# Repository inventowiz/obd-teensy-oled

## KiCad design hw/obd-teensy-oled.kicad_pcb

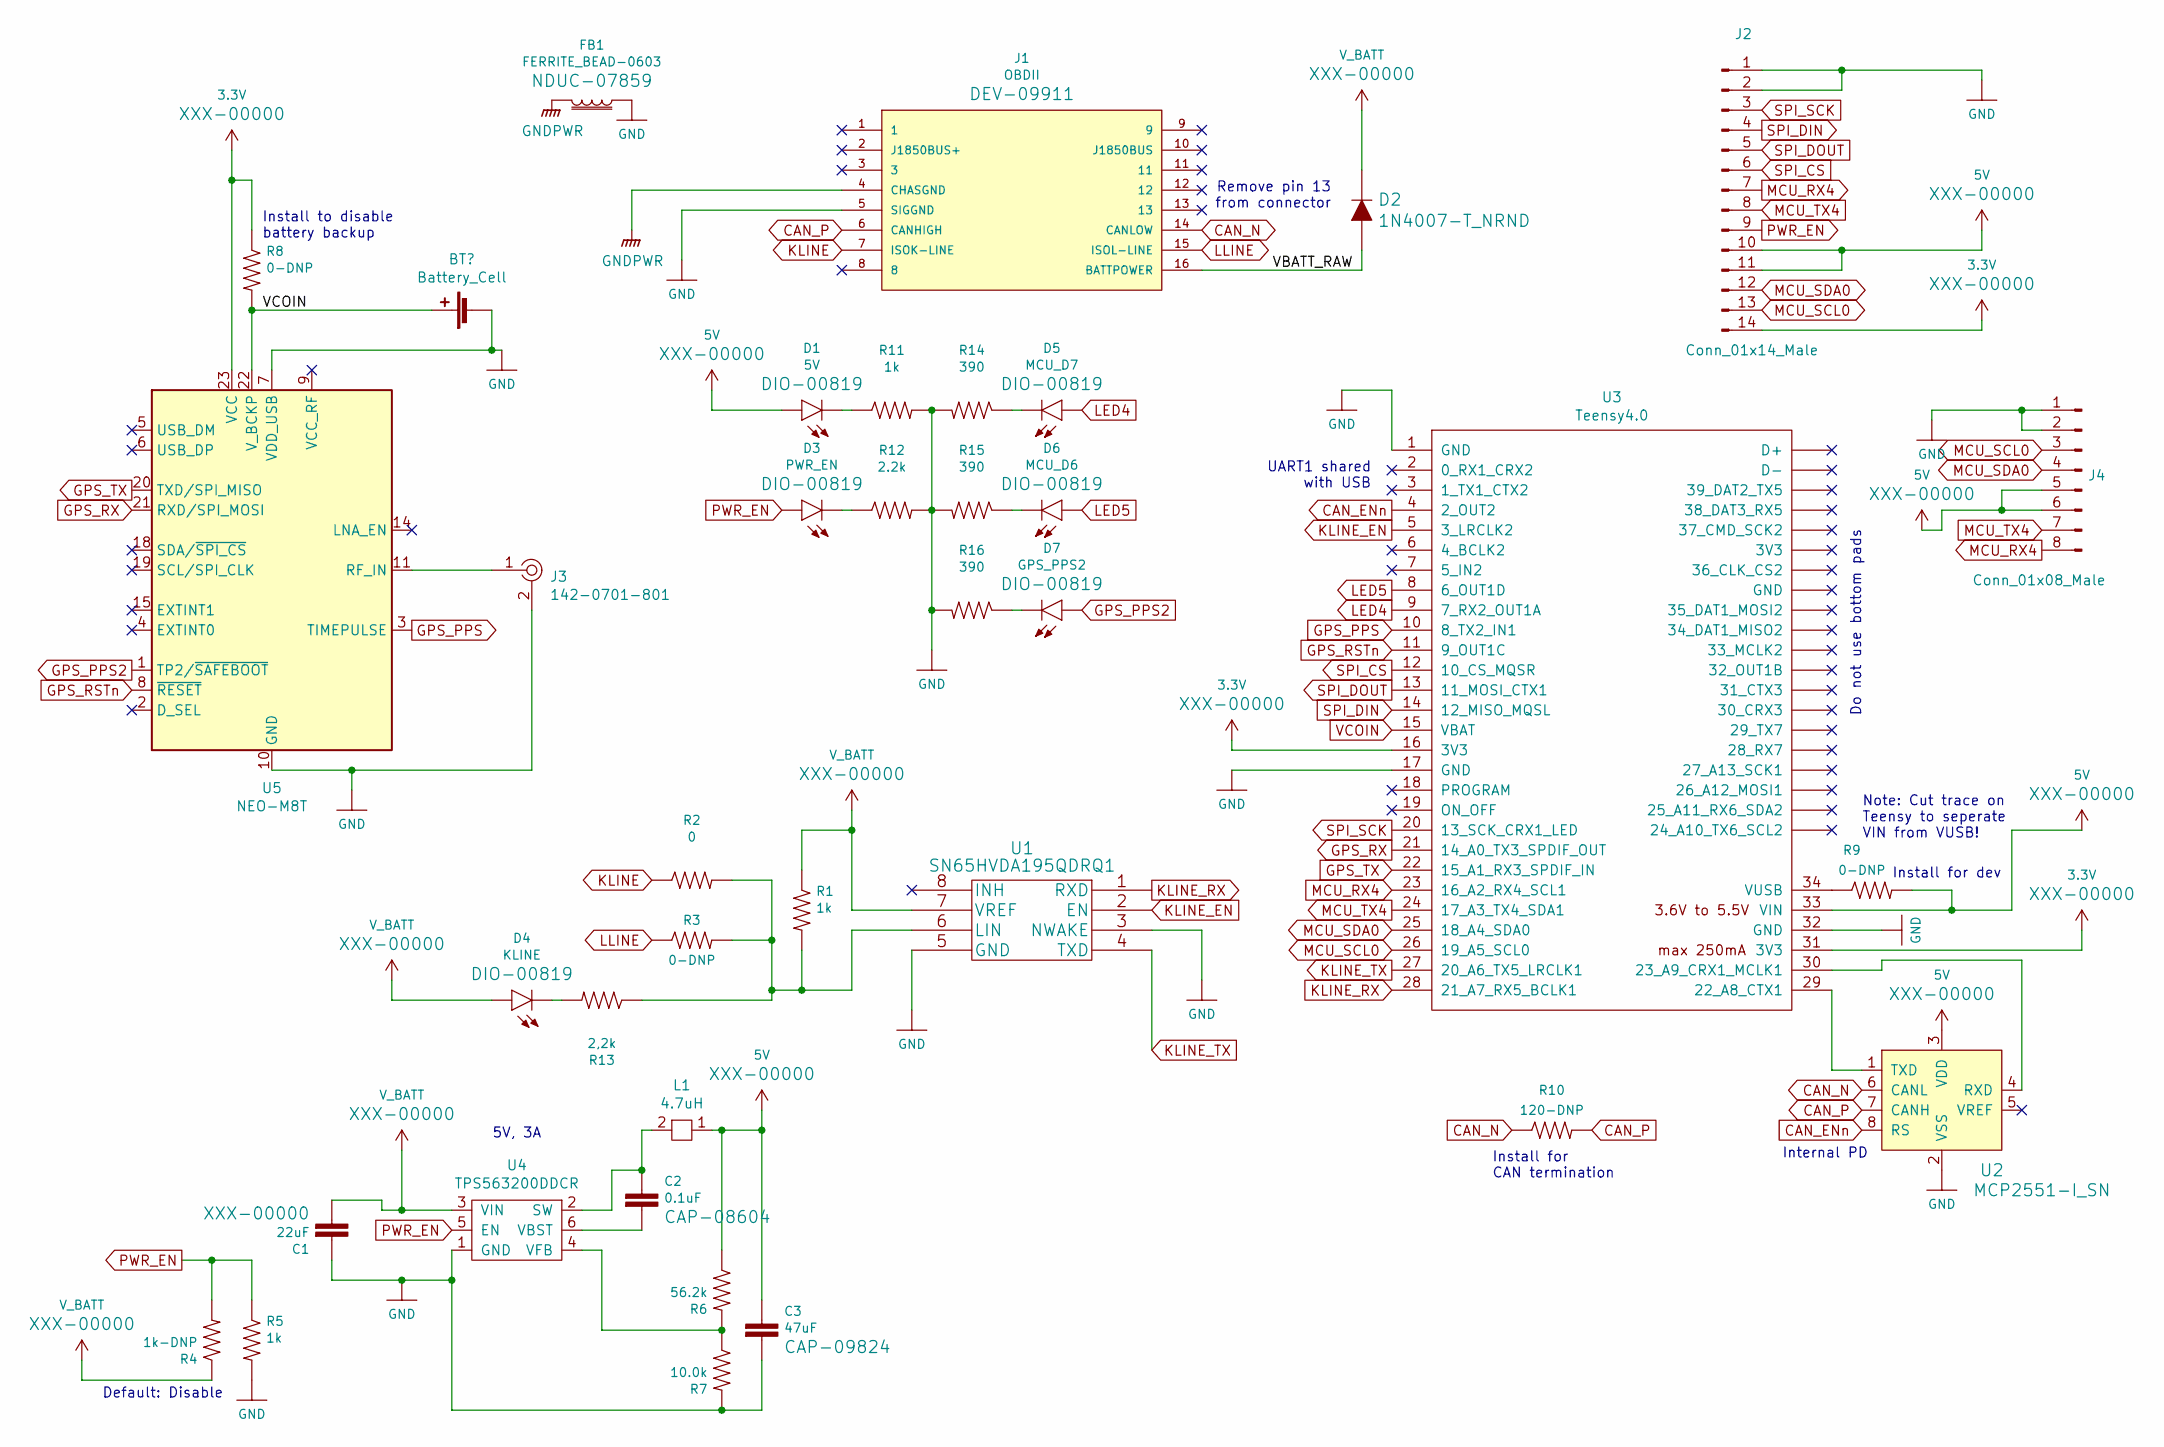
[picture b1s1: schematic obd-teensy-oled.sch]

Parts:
C1: 22uF; 1210
C2: 0.1uF; 0603
C3: 47uF; 1210
D1: 5V; LED-0603
D2: 1N4007-T_NRND; DO-41; MPN 1N4007-T; Digi-Key_PN 1N4007DICT-ND
D3: PWR_EN; LED-0603
D4: KLINE; LED-0603
D5: MCU_D7; LED-0603
D6: MCU_D6; LED-0603
D7: GPS_PPS2; LED-0603
FB1: FERRITE_BEAD-0603; 0603
J1: OBDII
J2: Conn_01x14_Male; Molex_PicoBlade_53048-1410_1x14_P1.25mm_Horizontal
J3: 142-0701-801; RF_SMA_BoardEdge_142-0701-801; MPN 142-0701-801; Digi-Key_PN J502-ND
J4: Conn_01x08_Male; Molex_PicoBlade_53047-0810_1x08_P1.25mm_Vertical
L1: 4.7uH; IHLP2020BZER4R7M11
R1, R5, R11: 1k; 0603
R2: 0; 0603
R3, R8, R9: 0-DNP; 0603
R4: 1k-DNP; 0603
R6: 56.2k; 0603
R7: 10.0k; 0603
R10: 120-DNP; 0603
R12: 2.2k; 0603
R13: 2,2k; 0603
R14, R15, R16: 390; 0603
U1: SN65HVDA195QDRQ1
U2: MCP2551-I_SN; SOIC-8_W3.9mm; MPN MCP2551-I/SN; Digi-Key_PN MCP2551-I/SN-ND
U3: Teensy4.0; Teensy40
U4: TPS563200DDCR; SOT-23-6
U5: NEO-M8T; ublox_NEO

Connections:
3.3V: J2.14, R8.1, U3.16 (3V3), U3.31 (3V3), U5.23 (VCC)
5V: C3.1, D1.A, J2.10, J2.11, J4.5, J4.6, L1.1, R6.1, R9.2, U2.3 (VDD), U3.33 (VIN)
/VBATT_RAW: D2.A, J1.16 (BATTPOWER)
CAN_ENn: U2.8 (RS), U3.4 (2_OUT2)
CAN_N: J1.14 (CANLOW), R10.1, U2.6 (CANL)
CAN_P: J1.6 (CANHIGH), R10.2, U2.7 (CANH)
GND: C1.2, C3.2, FB1.1, J1.5 (SIGGND), J2.1, J2.2, J3.2, J4.1, J4.2, R5.2, R7.2, R11.2, R12.2, R14.2, R15.2, R16.2, U1.3 (NWAKE), U1.5 (GND), U2.2 (VSS), U3.1 (GND), U3.17 (GND), U3.32 (GND), U4.1 (GND), U5.7 (VDD_USB), U5.10 (GND), U5.12 (GND), U5.13 (GND), U5.24 (GND); also elsewhere on the board
GNDPWR: FB1.2, J1.4 (CHASGND)
GPS_PPS: U3.10 (8_TX2_IN1), U5.3 (TIMEPULSE)
GPS_PPS2: D7.A, U5.1 (TP2/~SAFEBOOT)
GPS_RSTn: U3.11 (9_OUT1C), U5.8 (~RESET)
GPS_RX: U3.21 (14_A0_TX3_SPDIF_OUT), U5.21 (RXD/SPI_MOSI)
GPS_TX: U3.22 (15_A1_RX3_SPDIF_IN), U5.20 (TXD/SPI_MISO)
KLINE: J1.7 (ISOK-LINE), R2.1
KLINE_EN: U1.2 (EN), U3.5 (3_LRCLK2)
KLINE_RX: U1.1 (RXD), U3.28 (21_A7_RX5_BCLK1)
KLINE_TX: U1.4 (TXD), U3.27 (20_A6_TX5_LRCLK1)
LED4: D5.A, U3.9 (7_RX2_OUT1A)
LED5: D6.A, U3.8 (6_OUT1D)
LLINE: J1.15 (ISOL-LINE), R3.1
MCU_RX4: J2.7, J4.8, U3.23 (16_A2_RX4_SCL1)
MCU_SCL0: J2.13, J4.3, U3.26 (19_A5_SCL0)
MCU_SDA0: J2.12, J4.4, U3.25 (18_A4_SDA0)
MCU_TX4: J2.8, J4.7, U3.24 (17_A3_TX4_SDA1)
unnamed: C2.1, L1.2, U4.2 (SW)
unnamed: C2.2, U4.6 (VBST)
unnamed: D1.C, R11.1
unnamed: D3.C, R12.1
unnamed: D4.C, R13.2
unnamed: D5.C, R14.1
unnamed: D6.C, R15.1
unnamed: D7.C, R16.1
unnamed: J3.1, U5.11 (RF_IN)
unnamed: R1.2, R2.2, R3.2, R13.1, U1.6 (LIN)
unnamed: R6.2, R7.1, U4.4 (VFB)
unnamed: R9.1, U3.34 (VUSB)
unnamed: U2.1 (TXD), U3.29 (22_A8_CTX1)
unnamed: U2.4 (RXD), U3.30 (23_A9_CRX1_MCLK1)
PWR_EN: D3.A, J2.9, R4.2, R5.1, U4.5 (EN)
SPI_CS: J2.6, U3.12 (10_CS_MQSR)
SPI_DIN: J2.4, U3.14 (12_MISO_MQSL)
SPI_DOUT: J2.5, U3.13 (11_MOSI_CTX1)
SPI_SCK: J2.3, U3.20 (13_SCK_CRX1_LED)
VCOIN: R8.2, U3.15 (VBAT), U5.22 (V_BCKP); also elsewhere on the board
V_BATT: C1.1, D2.K, D4.A, R1.1, R4.1, U1.7 (VREF), U4.3 (VIN)

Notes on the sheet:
Note: Cut trace on Teensy to seperate VIN from VUSB!
Do not use bottom pads
Default: Disable
Install to disable battery backup
UART1 shared with USB
Install for dev
Install for CAN termination
Remove pin 13 from connector
Internal PD
5V, 3A

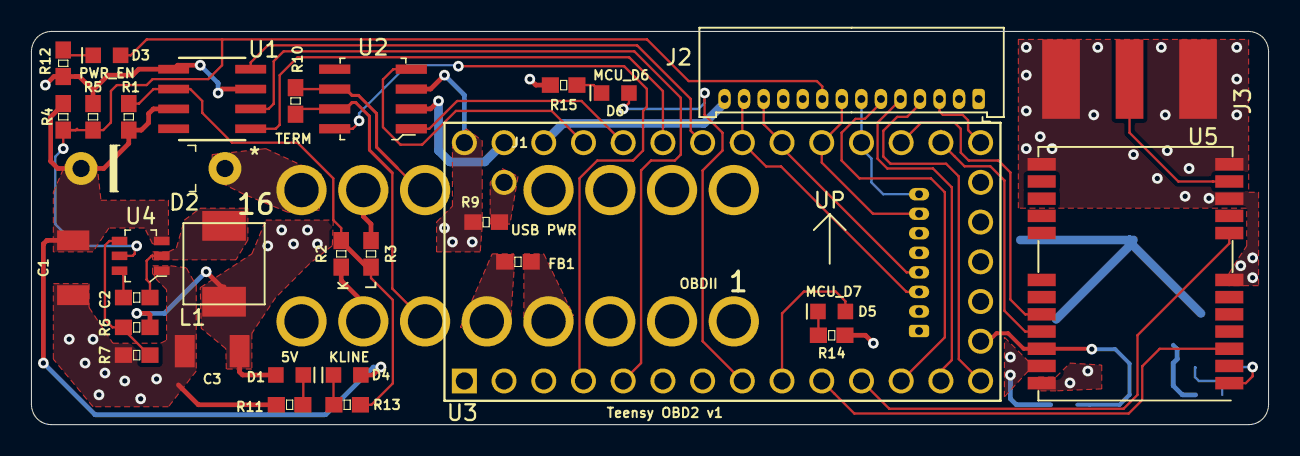
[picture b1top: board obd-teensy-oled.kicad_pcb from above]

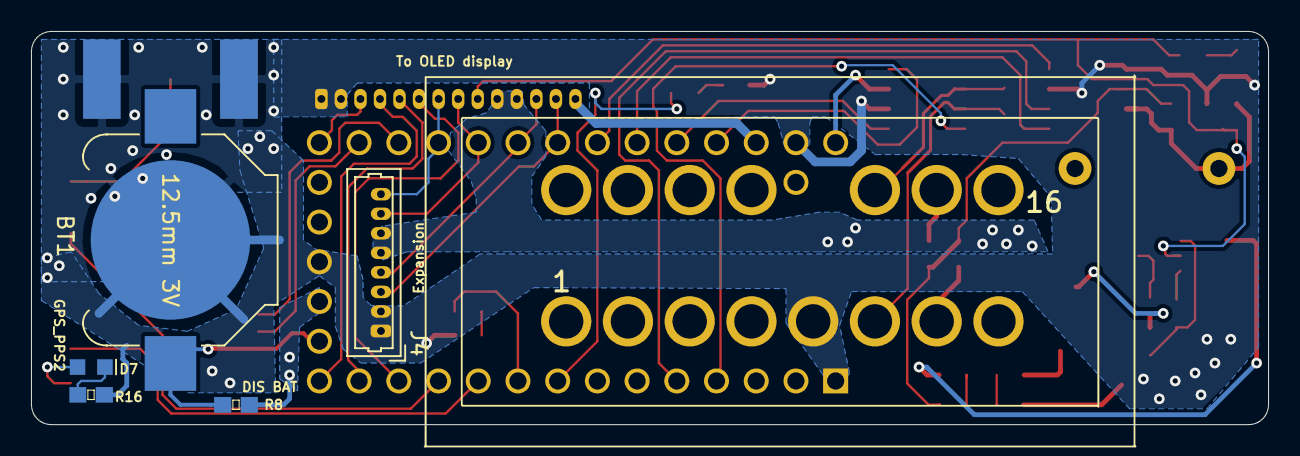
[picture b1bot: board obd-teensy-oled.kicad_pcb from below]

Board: 2 copper layers, 79.1 x 25.1 mm, 38 parts (5 on the bottom side), 45 nets.

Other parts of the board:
BT1: Battery_Cell; BatteryHolder_Keystone_3000_1x12mm

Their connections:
GND: BT1.2; also elsewhere on the board
VCOIN: BT1.1; also elsewhere on the board

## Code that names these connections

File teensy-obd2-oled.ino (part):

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#define OLED_CS     10
#define OLED_DC     19
#define OLED_RESET  18
#define CAN_ENn     2
#define KLINE_EN    3
#define LED5        6
#define LED4        7
#define GPS_PPS     8
#define GPS_RSTn    9
#define GPS_Serial  Serial3
#define Spare_Serial Serial4
#define KLINE_Serial Serial5
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void setup() {  
  // USB serial interface
  Serial.begin(115200);
  pinMode(LED5,OUTPUT);

  // GPS interface & RTC
  GPS_Serial.begin(9600);

  // CAN and KLINE
  pinMode(CAN_ENn,OUTPUT);
  digitalWrite(CAN_ENn,LOW); // turn on CAN tranceiver
  can.begin();
  can.setBaudRate(CAN_SPEED);
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  can.enableFIFO();
  
  // set up kline interface
  pinMode(KLINE_EN,OUTPUT);
  digitalWrite(KLINE_EN,HIGH); // turn on kline tranceiver
  KLINE_Serial.begin(4800);
  
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
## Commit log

2020-01-10 initial commit of hw and fw
2020-01-22 move some items around
2020-01-22 add enclosures to the repo
2020-03-29 some changes to software, working out kinks
2024-04-02 new oled library, new layout, begin radar work
2024-10-14 minor formatting tweaks

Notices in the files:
parts and their libraries:
Copyright 2016 Accelerated Designs. All rights reserved.
